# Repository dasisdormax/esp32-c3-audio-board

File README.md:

# WIP: esp32-c3-headset

## Components and data sheets

- ESP32-C3:
  - Series Datasheet: https://espressif.com/documentation/esp32-c3_datasheet_en.pdf
  - ESP32-C3-WROOM-02 Module Datasheet: https://www.espressif.com/documentation/esp32-c3-wroom-02_datasheet_en.pdf
- Battery:
  - Cell holder: Keystone 2460: https://www.keyelco.com/userAssets/file/Keystone-M70-FullVersion.pdf
  - Battery Charge controller MCP73831-2ACI-OT: http://ww1.microchip.com/downloads/en/DeviceDoc/20001984g.pdf
  - Battery protection: BQ29728: https://www.ti.com/lit/ds/symlink/bq2972.pdf
  - Battery charge/discharge MOSFET: DMG9926 https://www.diodes.com/assets/Datasheets/ds31770.pdf
- Power Supply:
  - p-channel enhancement MOSFET: DMP3165L https://www.diodes.com/assets/Datasheets/DMP3165L.pdf
  - TPS63031 Buck-Boost Converter: https://www.ti.com/lit/ds/symlink/tps63031.pdf
- Audio:
  - Connector: PJ320-D
  - Stereo Audio DAC: PCM5102: https://www.ti.com/lit/ds/symlink/pcm5102.pdf
  - Stereo Audio Amplifier: 
    - PAM8908: https://www.diodes.com/assets/Datasheets/products_inactive_data/PAM8908.pdf
    - Compatible alternative TPA6132A2: https://www.ti.com/lit/ds/symlink/tpa6132a2.pdf

## Licensing

Copyright © 2023 Maximilian Wende

- KiCad components: These are adapted from the KiCad Libraries and licensed [under the same terms](https://www.kicad.org/libraries/license/).
- Hardware design, documentation and remaining files: GNU General Public License, version 3 or later.

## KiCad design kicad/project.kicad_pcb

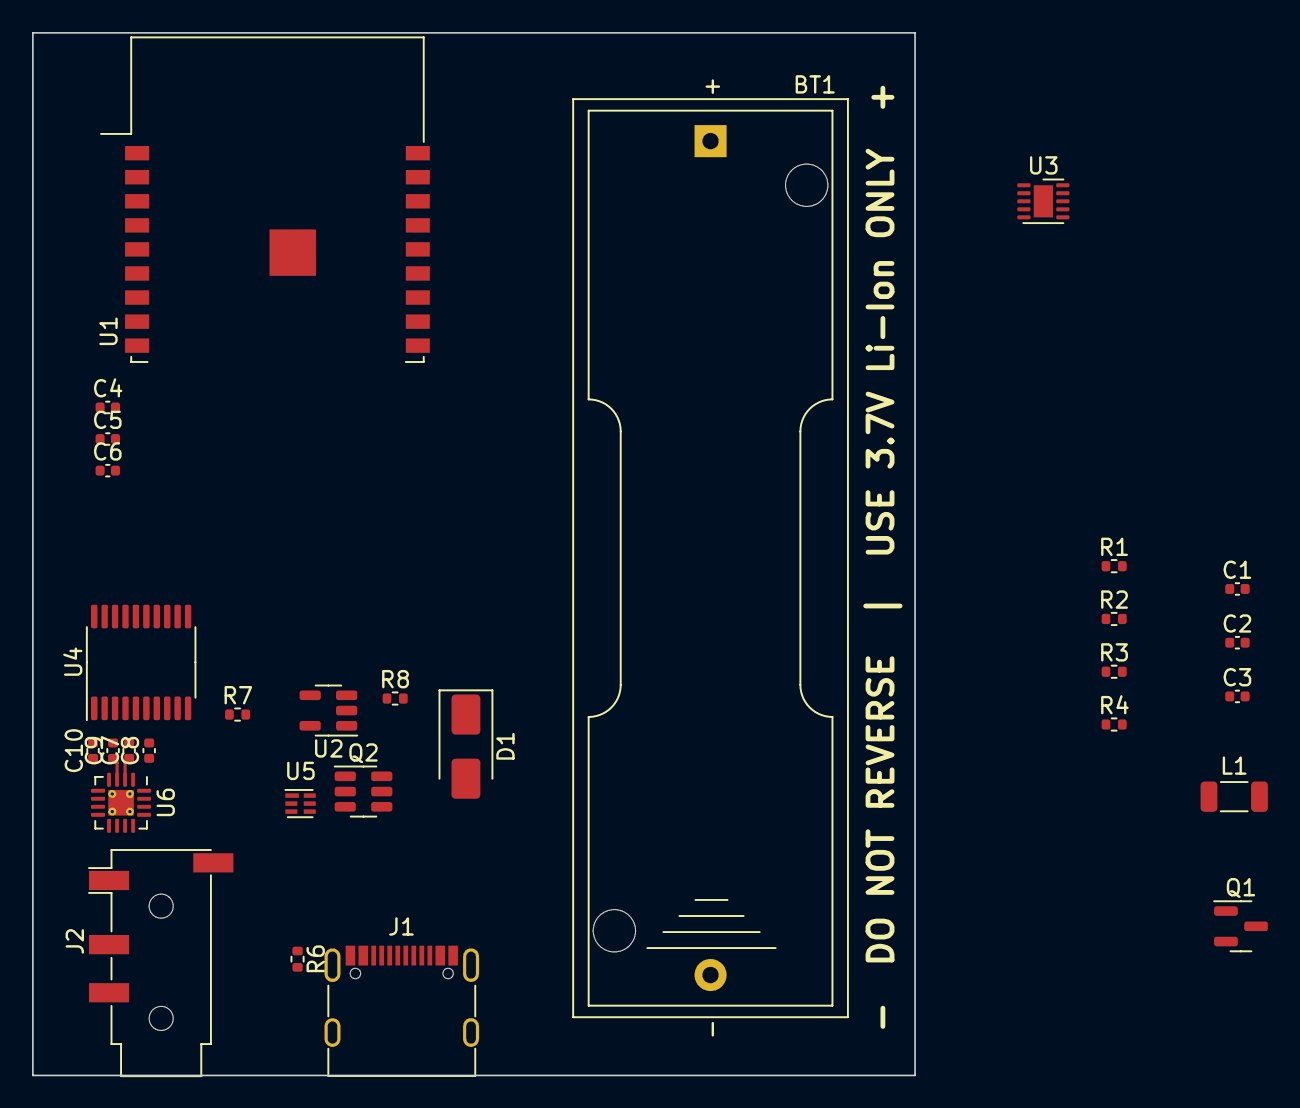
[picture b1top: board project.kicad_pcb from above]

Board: 4 copper layers, 55.0 x 65.0 mm, 30 parts (0 on the bottom side), 31 nets.

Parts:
BT1: Li-Ion; BatteryHolder_Keystone_2460_1xAA
C1, C2: 0.1u; C_0402_1005Metric
C3: 10u; C_0402_1005Metric
C4, C5, C6, C7, C8, C9, C10: 1u; C_0402_1005Metric
D1: SS54; D_SMA
J1: USB_C_Receptacle_USB2.0; USB_C_Receptacle_G-Switch_GT-USB-7010ASV
J2: AudioJack4; Jack_3.5mm_PJ320D_Horizontal
L1: 1.5u; L_1206_3216Metric
Q1: DMP3165L; SOT-23
Q2: DMG9926UDM; SOT-23-6
R1: 20k; R_0402_1005Metric
R2: 2k; R_0402_1005Metric
R3: 2.2k; R_0402_1005Metric
R4: 330; R_0402_1005Metric
R6: 1M; R_0402_1005Metric
R7, R8: 5.1k; R_0402_1005Metric
U1: ESP32-C3-WROOM-02
U2: MCP73831-2ACI-OT; SOT-23-5
U3: TPS63031DSK; WSON-10-1EP_2.5x2.5mm_P0.5mm_EP1.2x2mm
U4: PCM5102A; TSSOP-20_4.4x6.5mm_P0.65mm
U5: BQ29728; WSON-6_1.5x1.5mm_P0.5mm
U6: PAM8908; WQFN-16-1EP_3x3mm_P0.5mm_EP1.6x1.6mm_ThermalVias

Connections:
+3V3: U1.1 (3V3), U3.1 (VOUT), U3.10 (FB), U6.6 (G0), U6.14 (VDD)
+BATT: BT1.1 (+), Q1.3 (D), R4.2, U2.3 (V_{BAT})
-BATT: BT1.2 (-), C2.1, Q2.3 (S2), U5.4 (VSS)
/BS+: C2.2, R4.1, U5.5 (BAT)
/BS-: R3.1, U5.6 (V-)
/CC1: J1.A5 (CC1), R8.2
/CC2: J1.B5 (CC2), R7.1
/CG: Q2.6 (G1), U5.2 (Cout)
/CL: C8.2, U4.6 (OUTL)
/CPN: C6.2, U6.9 (CPN)
/CPP: C6.1, U6.11 (CPP)
/CR: C10.2, U4.7 (OUTR)
/D+: J1.A6 (D+), J1.B6 (D+), U1.14 (D+/IO19)
/D-: J1.A7 (D-), J1.B7 (D-), U1.13 (D-/IO18)
/DG: Q2.4 (G2), U5.3 (Dout)
/HPVDD: C4.2, U6.12 (HPVDD)
/HPVSS: C5.2, U6.8 (HPVSS)
/INL+: C7.1, U6.2 (INL+)
/INL-: C8.1, U6.1 (INL-)
/INR+: C9.1, U6.3 (INR+)
/INR-: C10.1, U6.4 (INR-)
/JL: J2.T, U6.16 (OUTL)
/JR: J2.R1, U6.5 (OUTR)
/PROG: R2.2, U2.5 (PROG)
/TPS_EN: C1.2, U3.6 (EN), U3.7 (PS/SYNC), U3.8 (VINA)
/TPS_IN: C3.1, D1.1 (K), Q1.2 (S), U3.5 (VIN)
GND: C1.1, C3.2, C4.1, C5.1, C7.2, C9.2, J1.A1 (GND), J1.A12 (GND), J1.B1 (GND), J1.B12 (GND), J2.R2, Q2.1 (D1), R1.2, R2.1, R3.2, R6.1, R7.2, R8.1, U1.19 (GND), U2.2 (V_{SS}), U3.3 (PGND), U3.9 (GND), U3.11 (PGND), U6.7 (G1), U6.10 (PGND), U6.15 (SGND)
unnamed: J1.S1 (SHIELD), R6.2
unnamed: L1.2, U3.4 (L1)
unnamed: L1.1, U3.2 (L2)
VBUS: D1.2 (A), J1.A4 (VBUS), J1.A9 (VBUS), J1.B4 (VBUS), J1.B9 (VBUS), Q1.1 (G), R1.1, U2.4 (V_{DD})

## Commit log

2023-06-03 Add initial KiCad project, assign license
2023-06-08 Add partial power management circuit
2023-06-12 Add USB-C, update power supply, add initial audio components
